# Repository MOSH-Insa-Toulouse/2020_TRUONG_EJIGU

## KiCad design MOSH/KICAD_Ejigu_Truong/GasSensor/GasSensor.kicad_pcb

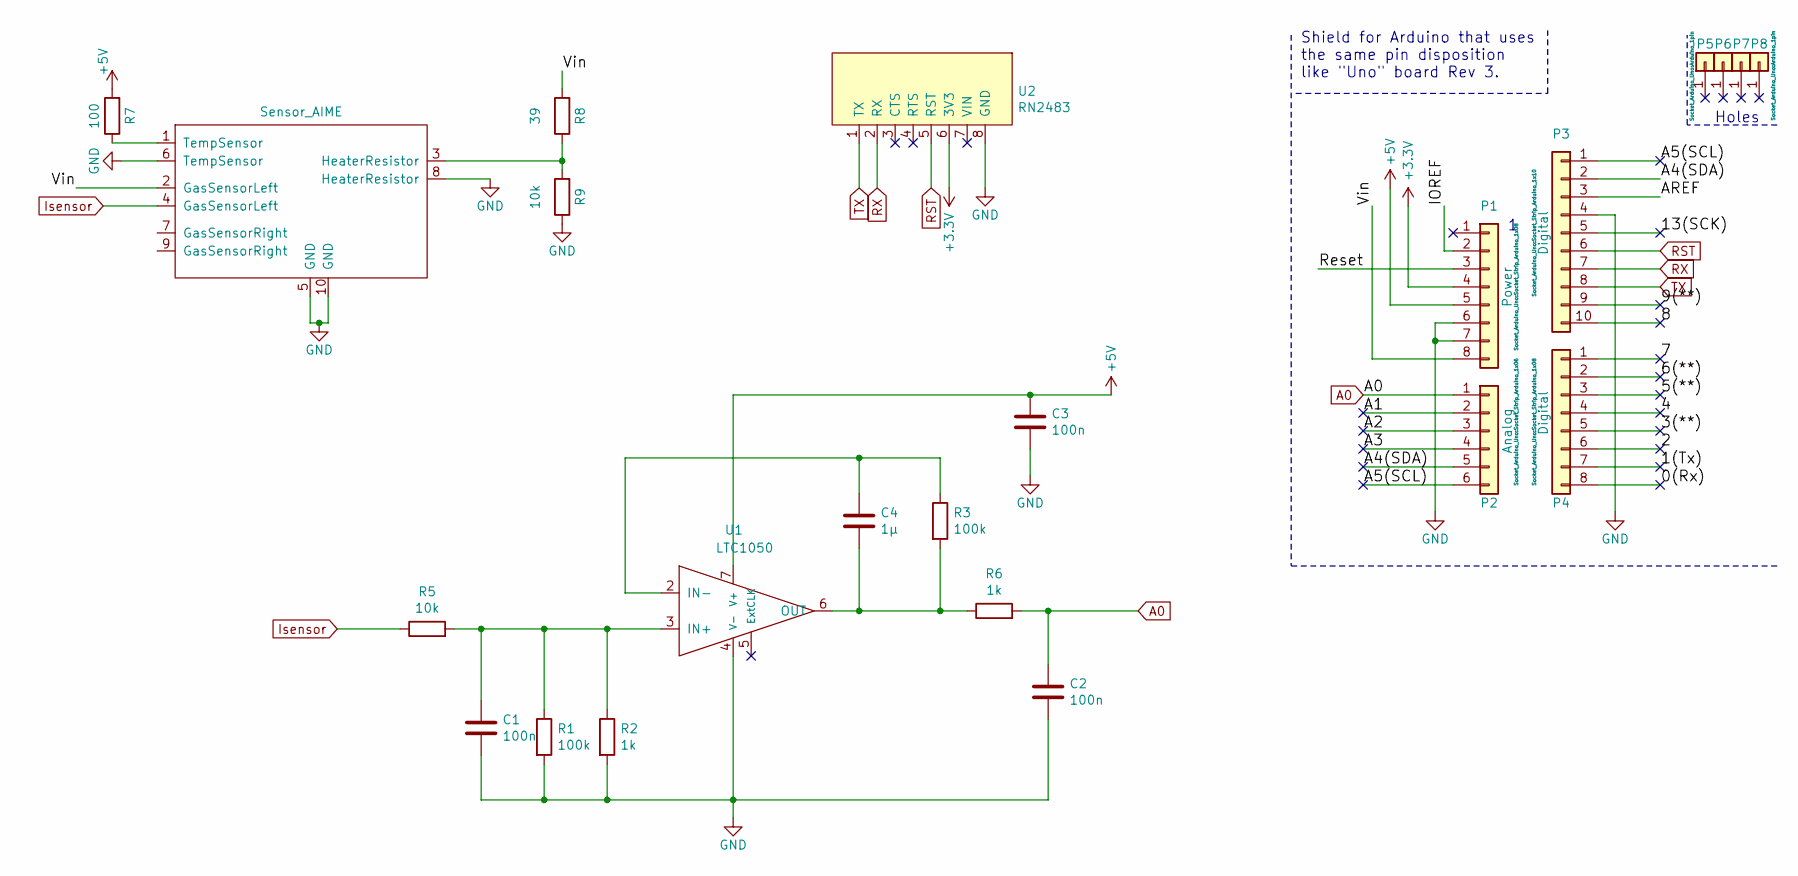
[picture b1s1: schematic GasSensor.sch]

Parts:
C1, C2, C3: 100n; C_Axial_L3.8mm_D2.6mm_P7.50mm_Horizontal
C4: 1µ; C_Axial_L3.8mm_D2.6mm_P7.50mm_Horizontal
GasSensor1: Sensor_AIME; to-5-10_window
P1: Power; Socket_Strip_Arduino_1x08
P2: Analog; Socket_Strip_Arduino_1x06
P3: Digital; Socket_Strip_Arduino_1x10
P4: Digital; Socket_Strip_Arduino_1x08
P5, P6, P7, P8: CONN_01X01; Arduino_1pin
R1, R3: 100k; R_Axial_DIN0204_L3.6mm_D1.6mm_P7.62mm_Horizontal
R2, R6: 1k; R_Axial_DIN0204_L3.6mm_D1.6mm_P7.62mm_Horizontal
R5, R9: 10k; R_Axial_DIN0204_L3.6mm_D1.6mm_P7.62mm_Horizontal
R7: 100; R_Axial_DIN0204_L3.6mm_D1.6mm_P7.62mm_Horizontal
R8: 39; R_Axial_DIN0204_L3.6mm_D1.6mm_P7.62mm_Horizontal
U1: LTC1050; AOP
U2: RN2483

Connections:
+3V3: P1.4, U2.6 (3V3)
+5V: C3.1, P1.5, R7.2, U1.7 (V+)
/0(Rx): P4.8
/1(Tx): P4.7
/2: P4.6
/3(**): P4.5
/4: P4.4
/5(**): P4.3
/6(**): P4.2
/7: P4.1
/8: P3.10
/9(**): P3.9
/13(SCK): P3.5
/A1: P2.2
/A2: P2.3
/A3: P2.4
/A4(SDA): P2.5, P3.2
/A5(SCL): P2.6, P3.1
/AREF: P3.3
/IOREF: P1.2
/Reset: P1.3
/Vin: GasSensor1.2 (GasSensorLeft), P1.8, R8.2
A0: C2.1, P2.1, R6.2
GND: C1.2, C2.2, C3.2, GasSensor1.5 (GND), GasSensor1.6 (TempSensor), GasSensor1.8 (HeaterResistor), GasSensor1.10 (GND), P1.6, P1.7, P3.4, R1.2, R2.2, R9.1, U1.4 (V-), U2.8 (GND)
Isensor: GasSensor1.4 (GasSensorLeft), R5.1
unnamed: C1.1, R1.1, R2.1, R5.2, U1.3 (IN+)
unnamed: C4.1, R3.1, U1.2 (IN-)
unnamed: C4.2, R3.2, R6.1, U1.6 (OUT)
unnamed: GasSensor1.1 (TempSensor), R7.1
unnamed: GasSensor1.3 (HeaterResistor), R8.1, R9.2
RST: P3.6, U2.5 (RST)
RX: P3.7, U2.2 (RX)
TX: P3.8, U2.1 (TX)

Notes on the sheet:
Holes
Shield for Arduino that uses the same pin disposition like "Uno" board Rev 3.

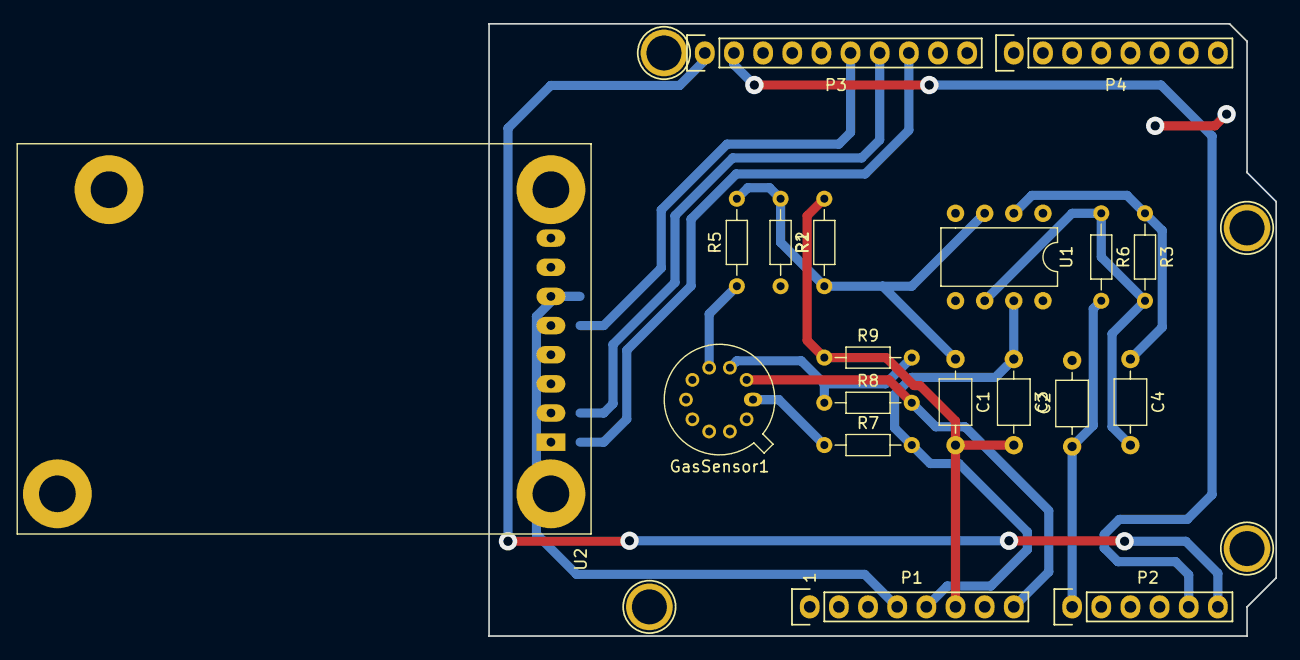
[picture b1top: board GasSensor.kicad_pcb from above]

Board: 2 copper layers, 68.6 x 53.3 mm, 23 parts (0 on the bottom side), 16 nets.
